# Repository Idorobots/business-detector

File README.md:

# Business Detector
A business card with a little mains AC voltage detector - proof of concept. Here's an early prototype PCB:

**Cons:**
- It's quite expensive for a business card.
- The battery socket makes the whole thing slightly thick.
- If you present it to pretty much anybody, they go straight to the nearest mains plug socket.

**Pros:**
- If you present it to somebody and they get electrocuted, you probably don't want to do business with them anyway. Bullet dodged.

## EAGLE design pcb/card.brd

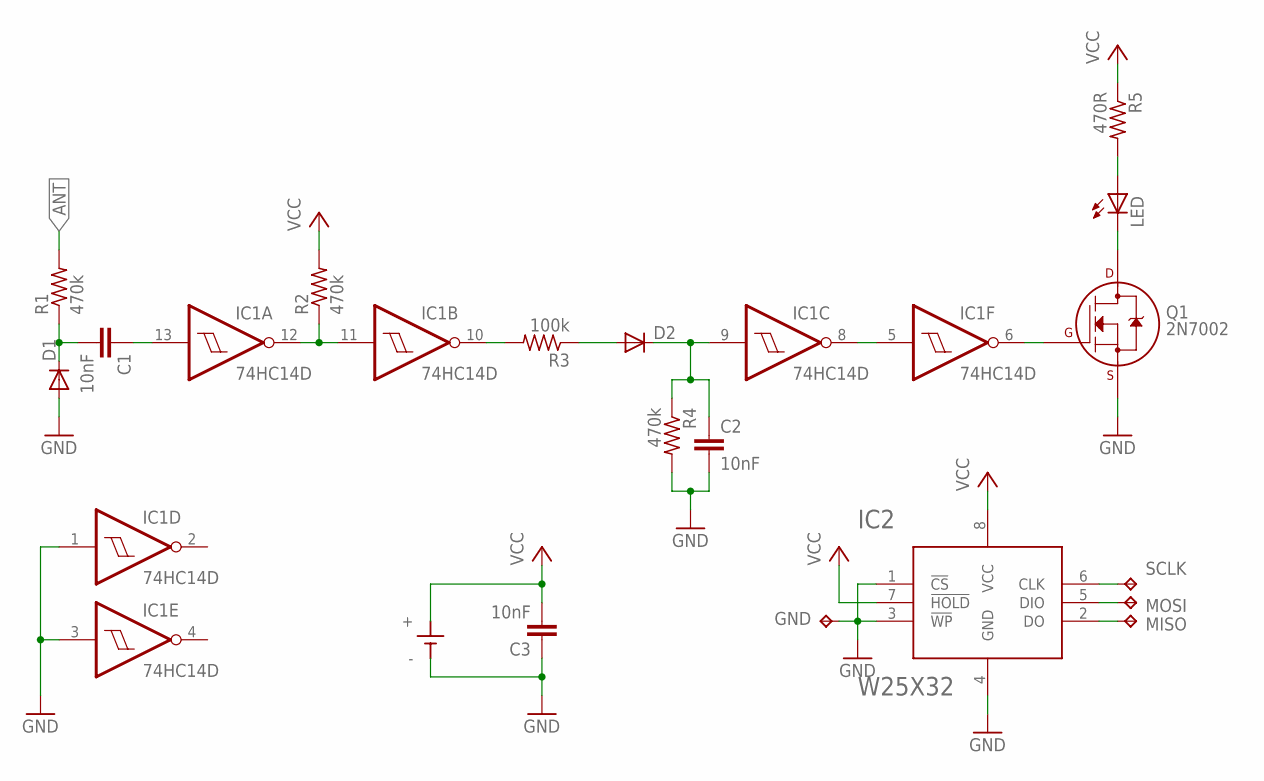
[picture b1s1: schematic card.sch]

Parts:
BAT: KB3003
C1, C2, C3: 10nF; C1206K
D1, D2: DIODE-MINIMELF; MINIMELF
GND: TPB1,27; B1,27
IC1: 74HC14D; SO14
IC2: W25X32; SOIC8
LED: LEDCHIPLED_1206; CHIPLED_1206
MISO: TPB1,27; B1,27
MOSI: TPB1,27; B1,27
Q1: 2N7002; SOT-23
R1, R2, R4: 470k; M1206
R3: 100k; M1206
R5: 470R; M1206
SCLK: TPB1,27; B1,27

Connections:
ANT: R1.2
GND: BAT.-, C2.2, C3.1, D1.A, GND.TP, IC1.1 (I), IC1.3 (I), IC1.7 (GND), IC2.1 (!CS!), IC2.3 (!WP!), IC2.4 (GND), Q1.2 (S), R4.2
unnamed: C1.1, IC1.13 (I)
unnamed: C1.2, D1.C, R1.1
unnamed: LED.A, R5.2
unnamed: LED.C, Q1.3 (D)
unnamed: IC1.11 (I), IC1.12 (O), R2.1
unnamed: IC1.10 (O), R3.2
unnamed: D2.A, R3.1
unnamed: C2.1, D2.C, IC1.9 (I), R4.1
unnamed: IC2.5 (DIO), MOSI.TP
unnamed: IC2.6 (CLK), SCLK.TP
unnamed: IC1.5 (I), IC1.8 (O)
unnamed: IC1.6 (O), Q1.1 (G)
unnamed: IC2.2 (DO), MISO.TP
VCC: BAT.+@1 (+), BAT.+@2 (+), C3.2, IC1.14 (VCC), IC2.7 (!HOLD!), IC2.8 (VCC), R2.2, R5.1

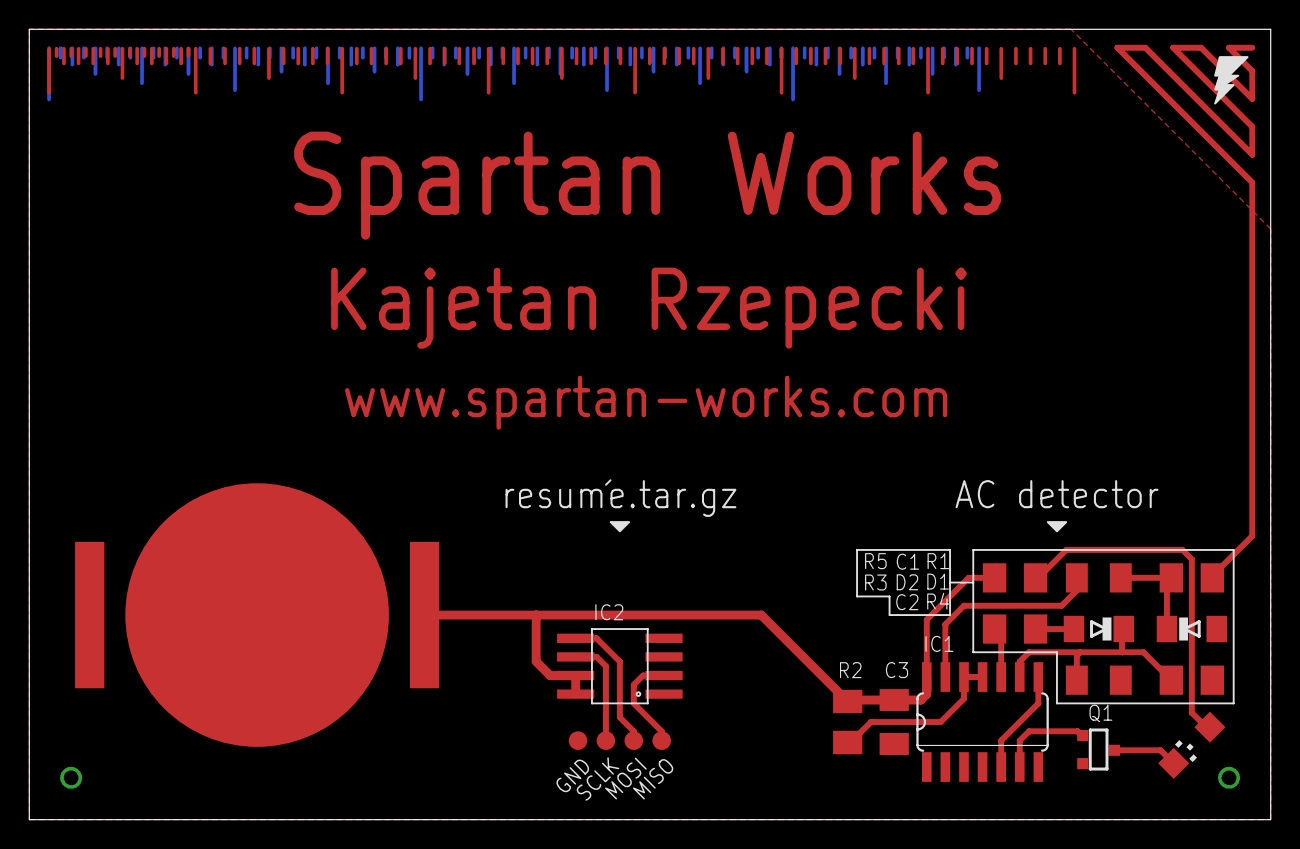
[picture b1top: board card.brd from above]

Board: 2 copper layers, 84.8 x 54.0 mm, 19 parts (0 on the bottom side), 15 nets.

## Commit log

2016-04-27 Added a schematic of the AC detector.
2016-04-27 Added EEPROM for resume storage.
2016-04-27 Added the PCB layout.
2016-04-27 Added a GND pad for the EEPROM chip.
2016-04-27 Optimized the design.
2016-04-28 Added a bypass cap & improved the layout.
2016-04-28 Apparently 10M Ohm is as high as it gets for reasonable amount of money.
2016-04-28 Improved the antenna.
2016-04-29 Added a battery holder part.
2016-04-29 Added the battery holder to the schematic.
2016-04-29 Adjusted the URL & its placement.
2016-04-29 Adjusted the PCB size & improved the design.
2016-04-29 Adjusted the soldermask expantion on the top layer text.
2016-04-30 Reduced spacing and changed the shape of resume testpads.
2016-04-30 Improved alignment of eye candy.
2016-05-01 Added a centigrade measure to the PCB edge.
2016-05-01 Added SPI Flash part.
2016-05-01 Swapped I2C EEPROM for SPI Flash & adjusted the design accordingly.
2016-05-01 Fixed misaligned centigrade measure wires.
2016-05-02 Added a current limitting resistor to the LED.
2016-05-02 Swapped the NPN tranny for a MOSFET.
2016-05-02 Compacted & improved the design.
2016-05-03 Added a back side to the card.
2016-05-06 Adjusted the SO8 package footprint to fit a 208-MIL SOIC.
2016-05-12 Added company name to the mix.
2016-07-29 Updated README with an image.
